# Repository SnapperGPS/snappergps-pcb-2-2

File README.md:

# snappergps-pcb-2-2-LiPo

This is an alternative version of the original SnapperGPS receiver.
Just like [V1.0.0](https://github.com/SnapperGPS/snappergps-pcb), [V2.0.0](https://github.com/SnapperGPS/snappergps-pcb-2), [V2.1.0](https://github.com/SnapperGPS/snappergps-pcb-2-1), and [V2.2.0](https://github.com/SnapperGPS/snappergps-pcb-2-2) it is a small, low-cost, and low-power GNSS receiver intended for non-real-time wildlife tracking.
It employs the snapshot GNSS technology, which offloads the computational expensive data processing to the cloud, and:

* Measures 26.3 mm x 28.5 mm,

* Operates on a lithium-ion polymer battery,

* Weighs about 8 g (without the battery),

* Has enough memory to provide about 22,000 position fixes,

* Captures fixes in user-defined time intervals or externally triggered,

* Needs only 12 ms of signal reception for a fix,

* Employs multiple satellite systems for high reliability (GPS, Galileo, and BeiDou),

* Achieves a median real-world tracking accuracy of about 15 m (before smoothing),

* Maintains a real-time clock to accurately timestamp the fixes,

* Measures the temperature in addition, and

* Is configured via USB in your browser without the need to install a driver or an app.

This repository contains the hardware design files that can be used to replicate a SnapperGPS receiver V2.2.0-LiPo.

If you use SnapperGPS hardware or software for research, please consider citing our publications.

For the hardware:

> Jonas Beuchert, Amanda Matthes, and Alex Rogers. 2023. SnapperGPS: Open Hardware for Energy-Efficient, Low-Cost Wildlife Location Tracking with Snapshot GNSS. Journal of Open Hardware, 7(1): 2, pp. 1–13. [https://doi.org/10.5334/joh.48](https://openhardware.metajnl.com/articles/10.5334/joh.48/).

For the cloud-processing software:

> Jonas Beuchert and Alex Rogers. 2021. SnapperGPS: Algorithms for Energy-Efficient Low-Cost Location Estimation Using GNSS Signal Snapshots. In SenSys ’21: ACM Conference on Embedded Networked Sensor Systems, November, 2021, Coimbra, Portugal. ACM, New York, NY, USA, 13 pages. https://doi.org/10.1145/3485730.3485931.

|  | 
|:--:| 
| *Figure 1: Top view (left) and bottom view (right) of assembled SnapperGPS receivers V2.2.0 with a passive ceramic patch antenna and holders for two LR48 or SR48 button cells. This version is similar to V2.1.0, but smaller.* |

**Table of Contents**

1. [Changes from previous versions](#changes-from-previous-versions)

2. [Workflow](#workflow)

3. [Getting started](#getting-started)

4. [Repository Structure](#repository-structure)

5. [Professional Manufacturing](#professional-manufacturing)

6. [Hand Assembly](#hand-assembly)

7. [Testing](#testing)

8. [Hardware Overview](#hardware-overview)

9. [Pinout](#pinout)

10. [Bill of Materials](#bill-of-materials)

11. [Additional Resources](#additional-resources)

## Changes from previous versions

The main changes from V1.0.0 are:

* The antenna is integrated into the PCB. No external active antenna is used anymore.

* The board is a bit smaller with 26.3 mm x 28.5 mm and this now includes the antenna.

* The memory is large enough to collect data for 22,000 fixes. Initially, V1.0.0 only supported a smaller memory for 11,000 fixes, although, it can now be upgraded to the larger memory version, too.

* The board (including antenna and excluding battery) weighs around 8 g. Depending on the choice of antenna and battery, this can be heavier or lighter than V1.0.0.

The main changes from V2.0.0 are:

* An optional external active antenna cannot be used anymore.

* No general-purpose input/output (GPIO) pins are exposed. Therefore, no daughter-board can be connected.

* The board is a bit smaller with 26.3 mm x 28.5 mm.

* The board does not have an option to use a thicker 4 mm antenna, just a thinner 2 mm antenna. This reduces signal quality in contrast to V2.0.0 with the 4 mm antenna.

* The board operates on a lithium-ion polymer battery rather than on coin cells.

The main changes from V2.1.0 and V2.2.0 are:

* The board is a bit smaller with 26.3 mm x 28.5 mm.

* The board operates on a lithium-ion polymer battery rather than on coin cells.

## Workflow

- Get/build your SnapperGPS receiver (see sections below).
- [Configure](https://snappergps.info/configure) your SnapperGPS receiver in your browser for your deployment.
- Deploy your SnapperGPS receiver.
- The SnapperGPS receiver captures GNSS snapshots according to your configuration.
- Recover your SnapperGPS receiver.
- [Upload](https://snappergps.info/upload) the data from your SnapperGPS receiver to our server.
- [Download](https://snappergps.info/view) the track of your surveilled animal.

## Getting started

You already have a SnapperGPS receiver?
See [here](GETTING-STARTED.md) how to get started.
The instructions are for V1.0.0, but V2.2.0-LiPo works very similar.

You need to build a receiver first? Keep reading.

## Repository Structure

The two files `.brd` and `.sch` are CAD files that contain the PCB's board design and schematic, respectively. They have been created with Autodesk EAGLE 9.6.2, but should be compatible with other electronic design software.

The directory `CAMOutputs` includes the Gerber files and drill file, which are necessary for PCB manufacturing.

The two files `.mnb` and `.mnt` can be used for a pick-and-place machine and describe the component positions and orientations on the bottom and top layer, respectively.

## Professional Manufacturing

The simplest way to replicate SnapperGPS is to upload the BOM, the Gerber files, the drill file, and the pick and place files to an online PCB manufacturing and assembly service. They will source the components, print the PCB, and assemble the board.

We recommend a thickness between 0.8 and 1.6 mm for the four-layered board. The thinner, the lighter.
The substrate can be FR-4 and hot air solder leveling (HASL) or electroless nickel immersion gold (ENIG) can be used for the finish.

You can find an FAQ on prefessional manufacturing in [the discussions forum](https://github.com/orgs/SnapperGPS/discussions/22).

## Hand Assembly

An alternative to prefessional manufacturing is to just obtain the SnapperGPS PCB from a PCB manufacturer and to manually assembly the board.
Hand-soldering a board takes less than 2 h for a skilled person, but requires intermediate equipment and skills and potentially additional time for testing, debugging, and re-work.

You can find instructions [here](https://github.com/SnapperGPS/snappergps-pcb/blob/main/README.md#hand-assembly).

## Testing

Some basic testing:

* Open [the SnapperGPS web app](https://snappergps.info) in Microsoft Edge or Google Chrome or download it from [the Microsoft Store](https://apps.microsoft.com/store/detail/snappergps/9P9RPRS6LSMM) or [Google Play](https://play.google.com/store/apps/details?id=com.herokuapp.snapper_gps.twa). (Alternatively, you can also host the SnapperGPS web app yourself, as described in [the _snappergps-app_ repository](https://github.com/SnapperGPS/snappergps-app)).

* Go to the *Configure* page and click/tap on *Pair receiver*.

* The connected SnapperGPS receiver should now be selectable in a pop-up window.

* After pairing, confirm that the receiver information in the table on the top of the page is appropriate, including on-board time and firmware version. The snapshot count should be zero.

* Check the measured battery voltage in the table at the top of the *Configure* page. We recommend around 3 V before a long-term deployment.

* Select some configuration parameters in the app and click/tap on *Configure*.

* Disconnect the SnapperGPS receiver.

* Record a few snapshots outdoors.

* Reconnect the SnapperGPS receiver.

* Go to the *Upload* page and follow the instructions to upload the snapshots from the SnapperGPS receiver to the server. Please select only snapshots for processing that you collected outdoors.

* Once processing is complete, inspect the calculated track on the *Download* page. There are also links to some of our tracks for comparison.

Testing the localisation accuracy:

* Record some data outdoors at a location with known coordinates.

* Upload it via the SnapperGPS app.

* Calculate the horizontal error between the estimated locations and the ground truth.

* We obtained median errors of 10-12 m, depending on the scenario.

Measuring the power consumption:

* Configure a SnapperGPS receiver using the SnapperGPS app.

* Power the SnapperGPS receiver from an external DC source with 3 V.

* Place an ammeter in series with the source.

* The current should be around 1 μA if the board is sleeping and the maximum current should be around 25 mA when capturing a snapshot. The charge consumption for a single snapshot should be <0.3 μAh.

Testing the flash memory:

* Record the maximum of 21824 snapshots.

* Transfer them to a host computer using the *Transfer data* button on the *Upload* page of the SnapperGPS web app.

* Ensure that all 21824 snapshots have been transferred and are provided as download.

## Hardware Overview

Please have a look at our [paper](https://doi.org/10.5334/joh.48).

## Pinout

We expose the VDD, GND, RESET, SWCLK, and SWDIO pins of the MCU on the the PCB.
The last two allow for debugging or flashing using [Serial Wire Debug (SWD)](https://community.silabs.com/s/article/serial-wire-debug-swd-x).
All five circular pads have a spacing of 0.1 in and, hence, the same as common PCB headers.

All five pads are labelled on the silkscreen of the PCB.

```
┌───────────────────────────────┐
│   ○     ○     ○     ○     ○   │
│  GND  RESET SWCLK SWDIO  VDD  │
│                               │
```

## Bill of Materials

The table below lists the electronic components that are needed to assemble a single SnapperGPS board.

|Designator                                    |Qty|Manufacturer                  |Part #                                 |Description/Value                                            |Package/Footprint|Mounting Type|Notes                                                                          |Supplier URL                                                                                           |
|----------------------------------------------|--:|------------------------------|---------------------------------------|-------------------------------------------------------------|-----------------|-------------|-------------------------------------------------------------------------------|-------------------------------------------------------------------------------------------------------|
|C4, C8, C10, C12, C13, C14, C16, C17, C20, C23| 10|Murata                        |GRM155R60J104KA01D                     |Ceramic capacitor, 100 nF                                    |0402             |SMD          |                                                                               |https://www.digikey.com/en/products/detail/murata-electronics/GRM155R60J104KA01D/490-6287-1-ND/3845484 |
|C3, C5, C6, C7, C9                            |  5|Murata                        |GRM155R60J103KA01D                     |Ceramic capacitor, 10 nF                                     |0402             |SMD          |                                                                               |https://www.digikey.com/en/products/detail/murata-electronics/GRM155R60J103KA01D/490-6286-1-ND/3845483 |
|C21, C22                                      |  2|Murata                        |GRM1555C1H180JA01D                     |Ceramic capacitor, 18 pF                                     |0402             |SMD          |                                                                               |https://www.digikey.com/en/products/detail/murata-electronics/GRM1555C1H180JA01D/2854383               |
|C11, C19, C124, C125                          |  4|Murata                        |GRM188R60J105KA01D                     |Multi-layer ceramic capacitor, 1 uF, 6.3 V, X5R              |0603             |SMD          |                                                                               |https://www.digikey.com/en/products/detail/murata-electronics/GRM188R60J105KA01D/490-1550-1-ND/587755  |
|C18, C101, C102                               |  3|Murata                        |GRM185R60J475ME15D                     |Multi-layer ceramic capacitor, 4.7 uF, 6.3 V, X5R            |0603             |SMD          |                                                                               |https://www.digikey.com/en/products/detail/murata-electronics/GRM185R60J475ME15D/490-3892-1-ND/965934  |
|C15                                           |  1|Murata                        |GRM188R60J106KE47D                     |Multi-layer ceramic capacitor, 10 uF, 6.3 V, X5R             |0603             |SMD          |                                                                               |https://www.digikey.com/en/products/detail/murata-electronics/GRM188R60J106KE47D/490-12538-1-ND/5797528|
|L2                                            |  1|Murata                        |BLM15HB221SH1D                         |Ferrite bead                                                 |0402             |SMD          |                                                                               |https://www.digikey.com/en/products/detail/murata-electronics/BLM15HB221SH1D/6798444                   |
|R11, R12                                      |  2|Yageo                         |RC0402FR-0715RL                        |Resistor, 15R                                                |0402             |SMD          |                                                                               |https://www.digikey.com/en/products/detail/yageo/RC0402FR-0715RL/311-15LRCT-ND/2827914                 |
|R15, R16, R120                                |  3|Yageo                         |RC0402FR-071KL                         |Resistor, 1K                                                 |0402             |SMD          |                                                                               |https://www.digikey.com/en/products/detail/yageo/RC0402FR-071KL/726513                                 |
|R10, R13, R17                                 |  3|Yageo                         |RC0402FR-074K7L                        |Resistor, 4K7                                                |0402             |SMD          |                                                                               |https://www.digikey.com/en/products/detail/yageo/RC0402FR-074K7L/311-4-7KLRCT-ND/2827881               |
|R7, R8                                        |  2|Yageo                         |RC0402FR-075K1L                        |Resistor, 5K1                                                |0402             |SMD          |                                                                               |https://www.digikey.com/en/products/detail/yageo/RC0402FR-075K1L/726624                                |
|R18                                           |  1|Yageo                         |RC0402FR-076K8L                        |Resistor, 6K8                                                |0402             |SMD          |                                                                               |https://www.digikey.com/en/products/detail/yageo/RC0402FR-076K8L/311-6-80KLRCT-ND/729589               |
|R14, R19                                      |  2|Yageo                         |RC0402FR-0710KL                        |Resistor, 10K                                                |0402             |SMD          |                                                                               |https://www.digikey.com/en/products/detail/yageo/RC0402FR-0710KL/726523                                |
|R121                                          |  1|Yageo                         |RC0402FR-0725K5L                       |Resistor, 25.5K                                              |0402             |SMD          |                                                                               |                                                                                                       |
|R1, R2, R3, R4, R5, R6, R9                    |  7|Yageo                         |RC0402FR-07100KL                       |Resistor, 100K                                               |0402             |SMD          |                                                                               |https://www.digikey.com/en/products/detail/yageo/RC0402FR-07100KL/311-100KLRCT-ND/729473               |
|Q2                                            |  1|Jauch Quartz                  |Q 0,032768-JTX310-12,5-10-T1-HMR-50K-LF|Crystal, 32.768 kHz ±10 ppm, 12.5 pF, 50 kOhm                |2-SMD            |SMD          |Possible substitute: Epsom, X1A0001410004 FC-135R 32.768KHZ 9PF                |https://www.digikey.com/en/products/detail/jauch-quartz/Q-0-032768-JTX310-12-5-10-T1-HMR-50K-LF/8108077|
|D1                                            |  1|Rohm Semiconductor            |SML-D12M1WT86                          |LED, yellow-green, 572 nm, 2.2 V                             |0603             |SMD          |                                                                               |https://www.digikey.com/en/products/detail/rohm-semiconductor/SML-D12M1WT86/SML-D12M1WT86CT-ND/5843861 |
|D2                                            |  1|Rohm Semiconductor            |SML-D12U1WT86                          |LED, red, 620 nm, 2.2 V                                      |0603             |SMD          |                                                                               |https://www.digikey.com/en/products/detail/rohm-semiconductor/SML-D12U1WT86/SML-D12U1WT86CT-ND/5843858 |
|TCXO1                                         |  1|Connor Winfield               |D32G-016.368M                          |Temperature compensated oscillator, 16.384 MHz               |3.2x2.5          |SMD          |Possible substitutes: EPSON, X1G005441030112 or TXC Corporation, 7Q-16.368MBG-T|https://www.digikey.com/en/products/detail/connor-winfield/D32G-016-368M/3641696                       |
|U2                                            |  1|Skyworks Solutions Inc.       |SE4150L-R                              |RF receiver                                                  |24-QFN           |SMD          |                                                                               |https://octopart.com/se4150l-r-skyworks+solutions-20439429                                             |
|SAW1                                          |  1|Abracon LLC                   |AFS20A42-1575.42-T3                    |SAW filter, 1.575 GHz, BW 42 MHz                             |4-SMD            |SMD          |Possible substitute: AFS20A02-1575.42-T3                                       |https://www.digikey.com/en/products/detail/abracon-llc/AFS20A42-1575-42-T3/535-12069-1-ND/4075659      |
|U1                                            |  1|Silicon Labs                  |EFM32HG310F64G-C-QFN32R                |Microcontroller                                              |32-QFN           |SMD          |Possible substitutes: EFM32HG310F64G-A-QFN32R or EFM32HG310F64G-B-QFN32R       |https://www.digikey.com/en/products/detail/silicon-labs/EFM32HG310F64G-C-QFN32R/336-6165-1-ND/10314104 |
|U3                                            |  1|Nexperia                      |PRTR5V0U2AX,235                        |TVS diode, 5.5 V                                             |SOT143B          |SMD          |                                                                               |https://www.digikey.com/en/products/detail/nexperia-usa-inc/PRTR5V0U2AX235/1727-5862-1-ND/2698064      |
|IC1                                           |  1|Winbond Electronics           |W25N01GVZEIG                           |NAND flash, 1 GBit                                           |WSON-8           |SMD          |Possible substitute:  W25N512GVEIG (512 MBit)                                  |https://www.digikey.com/en/products/detail/winbond-electronics/W25N01GVZEIG-TR/5803931                 |
|Q1, Q3, Q4                                    |  3|Rohm Semiconductor            |TT8M1TR                                |Mosfet array N and P-channel, 20 V, 2.5 A, 1 W               |8-SMD            |SMD          |                                                                               |https://www.digikey.com/en/products/detail/rohm-semiconductor/TT8M1TR/5042837                          |
|J1                                            |  1|JAE Electronics               |DX07S016JA1R1500                       |USB-C receptacle connector, 24 Pins (16+8 dummy), right angle|                 |through-hole |                                                                               |https://www.digikey.com/en/products/detail/jae-electronics/DX07S016JA1R1500/11585731                   |
|ANT1                                          |  1|Taoglas                       |GP.1575.25.2.A.02                      |GPS/GALILEO patch antenna                                    |25x25            |through-hole |                                                                               |https://www.digikey.com/en/products/detail/taoglas-limited/GP-1575-25-2-A-02/2332643                   |
|U104                                          |  1|Ablic Inc.                    |S-1318D33-M5T1U4                       |3.3 V 100 mA voltage regulator                               |SOT-23-5         |SMD          |                                                                               |                                                                                                       |
|U105                                          |  1|Microchip Technology          |MCP73831T-2ACI/OT                      |Lithium-ion polymer battery charger                          |SOT-23-5         |SMD          |                                                                               |                                                                                                       |
|                                              |   |                              |                                       |                                                             |                 |             |                                                                               |                                                                                                       |

The BOM differs slightly from the one for initial SnapperGPS test boards, which was cheaper.
For example, we used cheaper TCXOs, the X1G005441030112 manufactured by EPSON or the 7Q-16.368MBG-T from the TXC Corporation, which cost around $2 instead of the expensive D32G-016.368M that costs $7-$8.
We had to introduce this change because of the on-going global supply chain disruptions and recommend to revert to one of the initial choices for replications, if possible, to reduce the overall cost.

## Additional resources

## Acknowledgements

This SnapperGPS receiver version was developed and is maintained by
[Jonas Beuchert](https://users.ox.ac.uk/~kell5462/).

##

This documentation is licensed under a
[Creative Commons Attribution 4.0 International License][cc-by].

[![CC BY 4.0][cc-by-image]][cc-by]

[cc-by]: http://creativecommons.org/licenses/by/4.0/
[cc-by-image]: https://i.creativecommons.org/l/by/4.0/88x31.png

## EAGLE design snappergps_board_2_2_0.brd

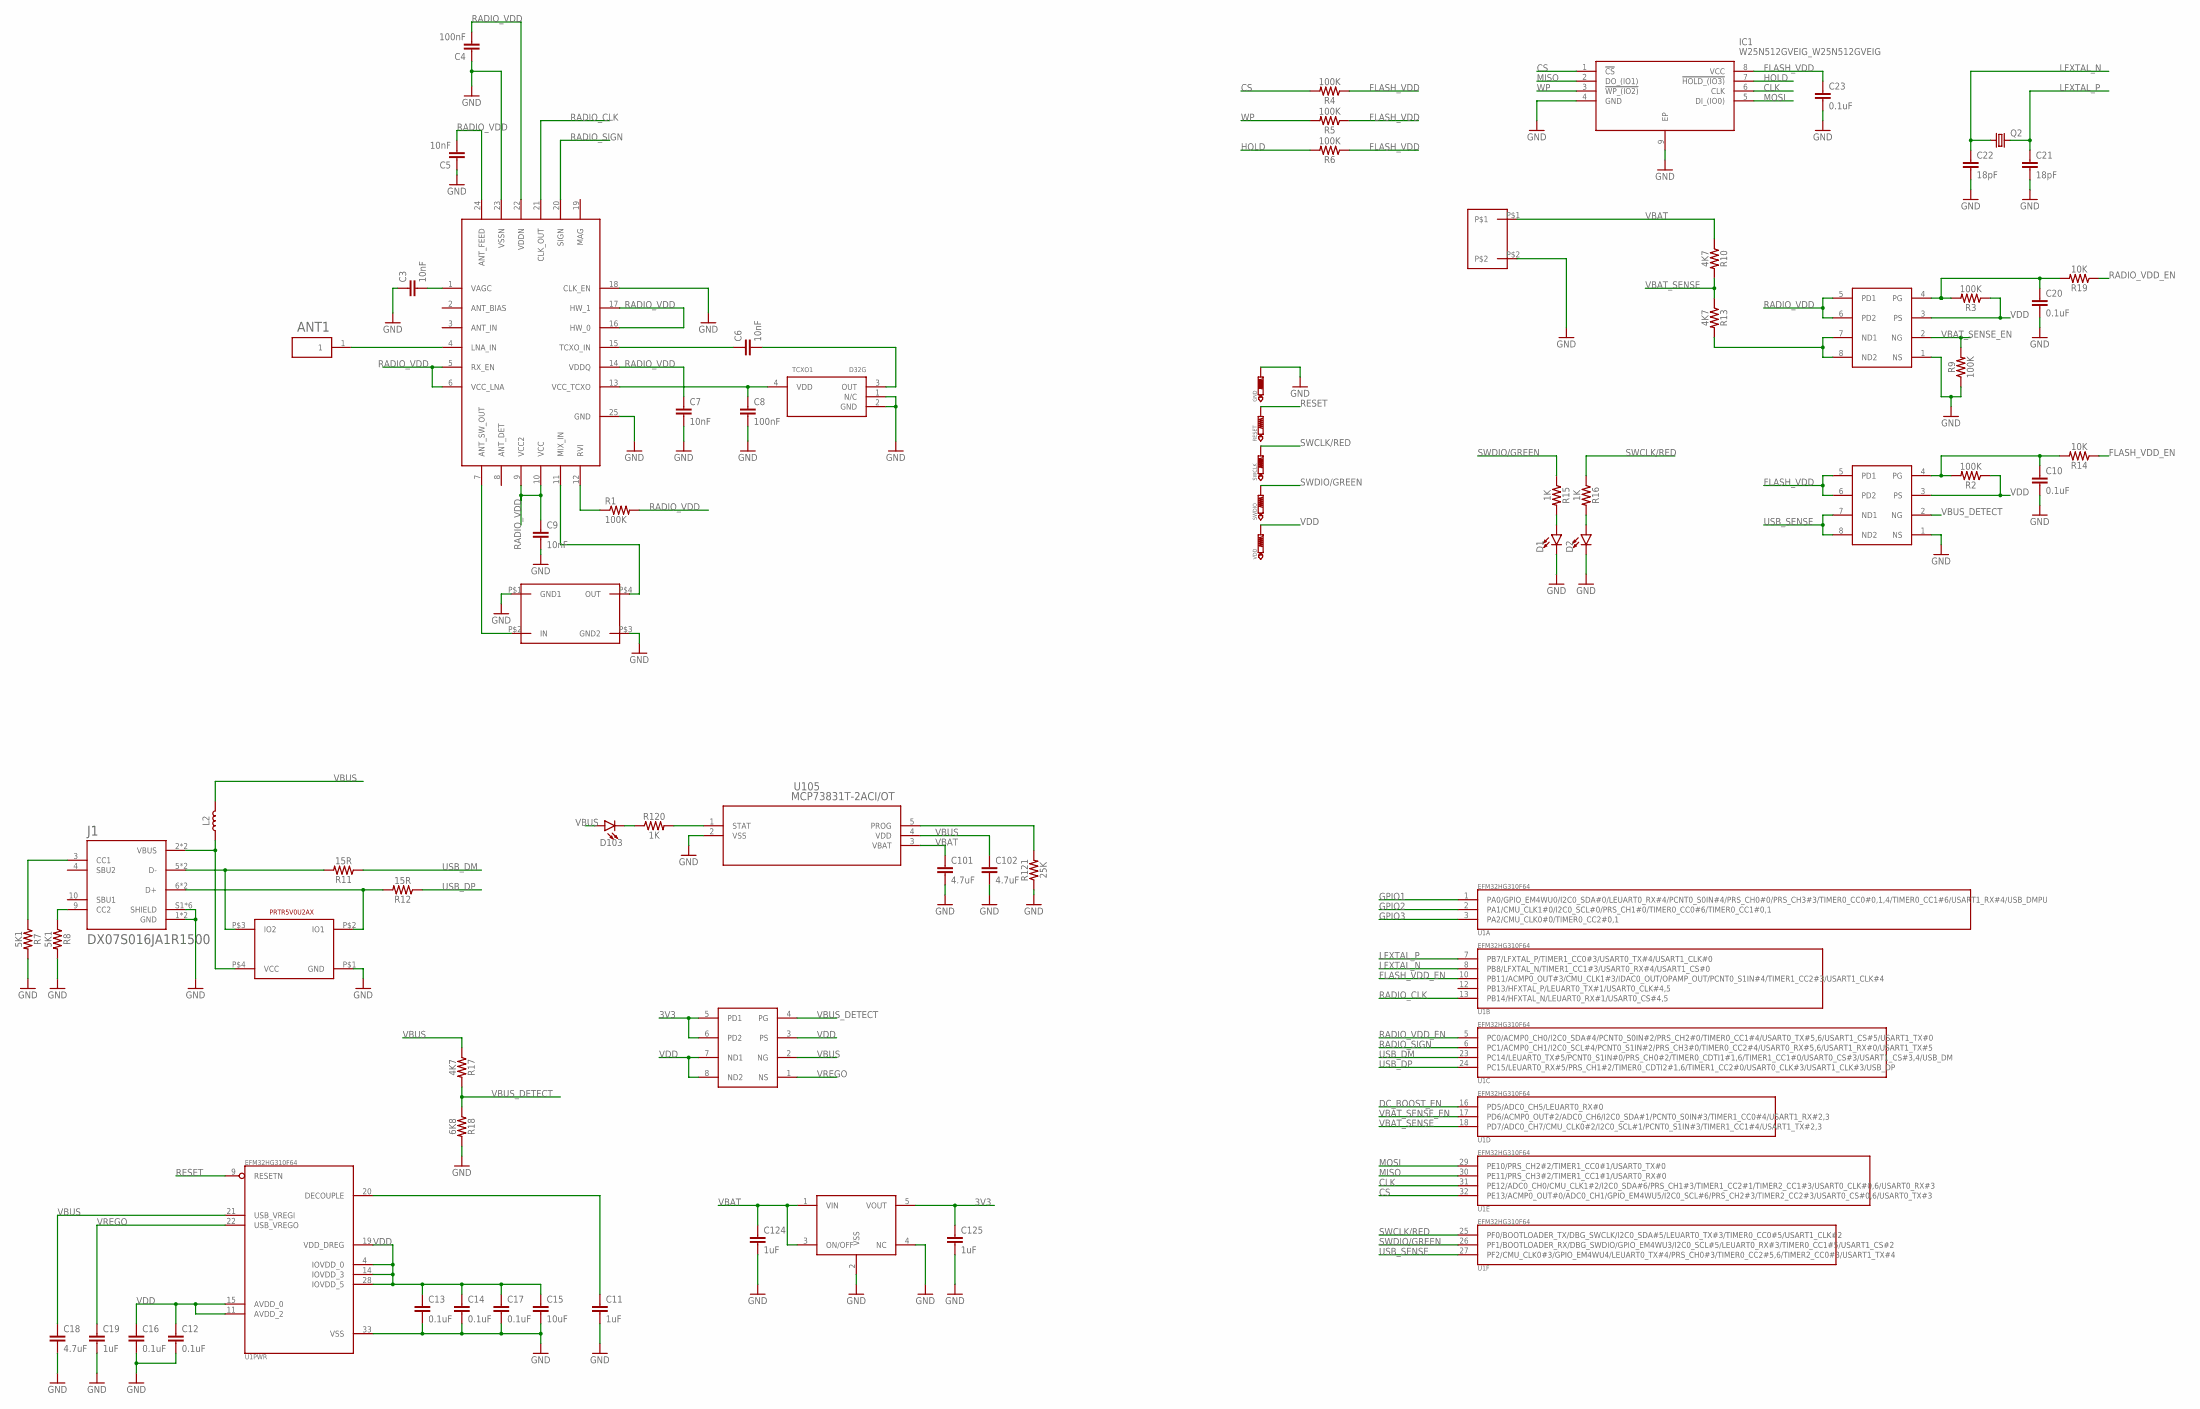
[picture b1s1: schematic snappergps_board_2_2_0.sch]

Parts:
ANT1: GP.1575.25.2.A.02; GP1575252A02
C3, C5, C6, C7, C9: 10nF; 0402
C4, C8: 100nF; 0402
C10, C12, C13, C14, C16, C17, C20, C23: 0.1uF; 0402
C11, C19, C124, C125: 1uF; 0603
C15: 10uF; 0603
C18, C101, C102: 4.7uF; 0603
C21, C22: 18pF; 0402
D1, D2, D103: LED0603; LED-0603
GND: PTR1B1,27; B1,27
IC1: W25N512GVEIG_W25N512GVEIG; W25N512GVEIG_SON127P800X600X80-9N
J1: DX07S016JA1R1500; JAE_DX07S016JA1R1500
L2: INDUCTOR; 0402
Q1, Q3, Q4: TT8M1TRAMANDA; AMANDA_TSST8
Q2: CRYSTAL_JTX310; 3.2X1.5
R1, R2, R3, R4, R5, R6, R9: 100K; 0402
R7, R8: 5K1; 0402
R10, R13, R17: 4K7; 0402
R11, R12: 15R; 0402
R14, R19: 10K; 0402
R15, R16, R120: 1K; 0402
R18: 6K8; 0402
R121: 25K; 0402
RESET: PTR1B1,27; B1,27
SAW1: SAW_FILTER
SWCLK: PTR1B1,27; B1,27
SWDIO: PTR1B1,27; B1,27
TCXO1: D32G
U1: EFM32HG310F64; QFN32
U2: RF_CIRCUIT-SE4150L; QFN50P400X400X90-25N
U3: TVS_DIODE-PRTR5V0U2AX
U104: S-1318D33-M5T1U4; SOT95P280X145-5N
U105: MCP73831T-2ACI/OT; SOT-23-5_MC_MCH
U$3: INDUCTION_BOARD_CONN2
VDD: PTR1B1,27; B1,27

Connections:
3V3: C125.1, Q4.5 (PD1), Q4.6 (PD2), U104.5 (VOUT)
CLK: IC1.6 (CLK), U1.31 (PE12/ADC0_CH0/CMU_CLK1#2/I2C0_SDA#6/PRS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)
CS: IC1.1 (!CS), R4.2, U1.32 (PE13/ACMP0_OUT#0/ADC0_CH1/GPIO_EM4WU5/I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)
DC_BOOST_EN: U1.16 (PD5/ADC0_CH5/LEUART0_RX#0)
FLASH_VDD: C23.1, IC1.8 (VCC), Q3.5 (PD1), Q3.6 (PD2), R4.1, R5.1, R6.1
FLASH_VDD_EN: R14.1, U1.10 (PB11/ACMP0_OUT#3/CMU_CLK1#3/IDAC0_OUT/O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)
GND: C3.1, C4.1, C5.1, C7.2, C8.2, C9.2, C10.2, C11.2, C12.2, C13.2, C14.2, C15.2, C16.2, C17.2, C18.2, C19.2, C20.2, C21.2, C22.2, C23.2, C101.2, C102.2, C124.2, C125.2, D1.C, D2.C, GND.TP, IC1.4 (GND), IC1.9 (EP), J1.1 (GND), J1.12 (GND), J1.S1 (SHIELD), J1.S2 (SHIELD), J1.S3 (SHIELD), J1.S4 (SHIELD), J1.S5 (SHIELD), J1.S6 (SHIELD), Q1.1 (NS), Q3.1 (NS), R7.2, R8.2, R9.1, R18.2, R121.1, SAW1.P$1 (GND1), SAW1.P$3 (GND2), TCXO1.1 (N/C), TCXO1.2 (GND), U1.33 (VSS), U2.18 (CLK_EN), U2.23 (VSSN), U2.25 (GND), U3.P$1 (GND), U104.2 (VSS), U104.4 (NC), U105.2 (VSS), U$3.P$2
GPIO1: U1.1 (PA0/GPIO_EM4WU0/I2C0_SDA#0/LEUART0_RX#4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)
GPIO2: U1.2 (PA1/CMU_CLK1#0/I2C0_SCL#0/PRS_CH1#0/TIM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)
GPIO3: U1.3 (PA2/CMU_CLK0#0/TIMER0_CC2#0,1)
HOLD: IC1.7 (!HOLD_(IO3)), R6.2
LFXTAL_N: C22.1, Q2.1, U1.8 (PB8/LFXTAL_N/TIMER1_CC1#3/USART0_RX#4/U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)
LFXTAL_P: C21.1, Q2.2, U1.7 (PB7/LFXTAL_P/TIMER1_CC0#3/USART0_TX#4/U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)
MISO: IC1.2 (DO_(IO1)), U1.30 (PE11/PRS_CH3#2/TIMER1_CC1#1/USART0_RX#0)
MIXIN: SAW1.P$4 (OUT), U2.11 (MIX_IN)
MOSI: IC1.5 (DI_(IO0)), U1.29 (PE10/PRS_CH2#2/TIMER1_CC0#1/USART0_TX#0)
unnamed: Q1.7 (ND1), Q1.8 (ND2), R13.2
unnamed: C20.1, Q1.4 (PG), R3.2, R19.2
unnamed: J1.9 (CC2), R8.1
unnamed: J1.3 (CC1), R7.1
unnamed: ANT1.1, U2.4 (LNA_IN)
unnamed: R1.1, U2.12 (RVI)
unnamed: D103.C, R120.1
unnamed: SAW1.P$2 (IN), U2.7 (ANT_SW_OUT)
unnamed: C8.1, TCXO1.4 (VDD), U2.13 (VCC_TCXO)
unnamed: C6.1, U2.15 (TCXO_IN)
unnamed: C6.2, TCXO1.3 (OUT)
unnamed: C11.1, U1.20 (DECOUPLE)
unnamed: C10.1, Q3.4 (PG), R2.2, R14.2
unnamed: R120.2, U105.1 (STAT)
unnamed: D1.A, R15.2
unnamed: D2.A, R16.2
unnamed: C3.2, U2.1 (VAGC)
unnamed: R121.2, U105.5 (PROG)
unnamed: J1.2 (VBUS), J1.11 (VBUS), L2.1, U3.P$4 (VCC)
unnamed: J1.6 (D+), J1.7 (D+), R12.2, U3.P$2 (IO1)
unnamed: J1.5 (D-), J1.8 (D-), R11.2, U3.P$3 (IO2)
RADIO_CLK: U1.13 (PB14/HFXTAL_N/LEUART0_RX#1/USART0_CS#4,5), U2.21 (CLK_OUT)
RADIO_SIGN: U1.6 (PC1/ACMP0_CH1/I2C0_SCL#4/PCNT0_S1IN#2/P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), U2.20 (SIGN)
RADIO_VDD: C4.2, C5.2, C7.1, C9.1, Q1.5 (PD1), Q1.6 (PD2), R1.2, U2.5 (RX_EN), U2.6 (VCC_LNA), U2.9 (VCC2), U2.10 (VCC), U2.14 (VDDQ), U2.16 (HW_0), U2.17 (HW_1), U2.22 (VDDN), U2.24 (ANT_FEED)
RADIO_VDD_EN: R19.1, U1.5 (PC0/ACMP0_CH0/I2C0_SDA#4/PCNT0_S0IN#2/P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)
RESET: RESET.TP, U1.9 (RESETN)
SWCLK/RED: R16.1, SWCLK.TP, U1.25 (PF0/BOOTLOADER_TX/DBG_SWCLK/I2C0_SDA#5/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)
SWDIO/GREEN: R15.1, SWDIO.TP, U1.26 (PF1/BOOTLOADER_RX/DBG_SWDIO/GPIO_EM4WU3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)
USB_DM: R11.1, U1.23 (PC14/LEUART0_TX#5/PCNT0_S1IN#0/PRS_CH0#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)
USB_DP: R12.1, U1.24 (PC15/LEUART0_RX#5/PRS_CH1#2/TIMER0_CDTI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)
USB_SENSE: Q3.7 (ND1), Q3.8 (ND2), U1.27 (PF2/CMU_CLK0#3/GPIO_EM4WU4/LEUART0_TX#4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)
VBAT: C101.1, C124.1, R10.1, U104.1 (VIN), U104.3 (ON/OFF), U105.3 (VBAT), U$3.P$1
VBAT_SENSE: R10.2, R13.1, U1.18 (PD7/ADC0_CH7/CMU_CLK0#2/I2C0_SCL#1/PCNT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)
VBAT_SENSE_EN: Q1.2 (NG), R9.2, U1.17 (PD6/ACMP0_OUT#2/ADC0_CH6/I2C0_SDA#1/PCN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)
VBUS: C18.1, C102.1, D103.A, L2.2, Q4.2 (NG), R17.1, U1.21 (USB_VREGI), U105.4 (VDD)
VBUS_DETECT: Q3.2 (NG), Q4.4 (PG), R17.2, R18.1
VDD: C12.1, C13.1, C14.1, C15.1, C16.1, C17.1, Q1.3 (PS), Q3.3 (PS), Q4.3 (PS), Q4.7 (ND1), Q4.8 (ND2), R2.1, R3.1, U1.4 (IOVDD_0), U1.11 (AVDD_2), U1.14 (IOVDD_3), U1.15 (AVDD_0), U1.19 (VDD_DREG), U1.28 (IOVDD_5), VDD.TP
VREGO: C19.1, Q4.1 (NS), U1.22 (USB_VREGO)
WP: IC1.3 (!WP_(IO2)), R5.2

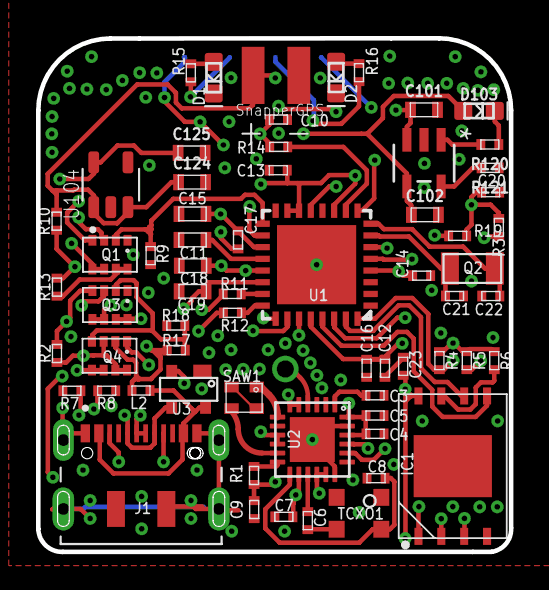
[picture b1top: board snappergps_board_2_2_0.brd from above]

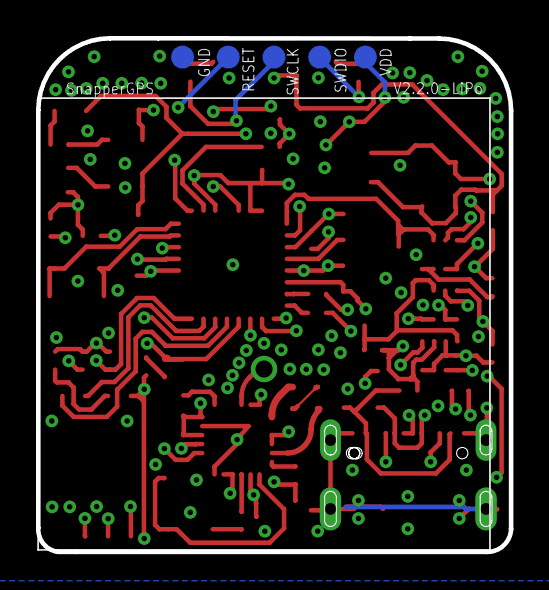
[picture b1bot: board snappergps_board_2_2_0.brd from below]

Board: 4 copper layers, 26.3 x 28.5 mm, 70 parts (6 on the bottom side), 51 nets.

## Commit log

2023-09-14 Add license, centroid files, images
2023-09-14 Add gerber and drill files
2023-09-14 Rename centroid files, add design files
2023-09-14 Tweak schematic
2023-09-14 Add image for readme
2023-09-14 Update pinout in README
2023-09-17 Update accuracy
2024-03-03 Replace coin cells with lipo, add lipo charger
2024-03-03 Update board layout
2024-03-03 Add manufacturing files & tweak PCB
2024-03-04 Update README.md with WIP note and fixed versioning
2024-03-11 Fix component number and white space
2024-03-11 Add -/+ to silkscreen; tweak wiring
2024-07-08 Remove WIP tag
2025-08-21 Update README.md with SAW sub

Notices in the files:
README.md:
This documentation is licensed under a
[Creative Commons Attribution 4.0 International License][cc-by].
CC BY 4.0
parts and their libraries:
EFM32: CC0 License
COPYRIGHT: Copyright (C) 2024 Ultra Librarian. All rights reserved.
SparkFun-Aesthetics: Licensing: Creative Commons ShareAlike 4.0 International - https://creativecommons.org/licenses/by-sa/4.0
